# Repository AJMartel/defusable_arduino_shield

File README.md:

# Defusable Alarm Clock Shield for Arduino

Deze github bevat de software, datasheets en referentie materiaal incl. printplaat bestanden van het Defusable Alarm Clock Shield voor Arduino.

J.A. Korten - 2017

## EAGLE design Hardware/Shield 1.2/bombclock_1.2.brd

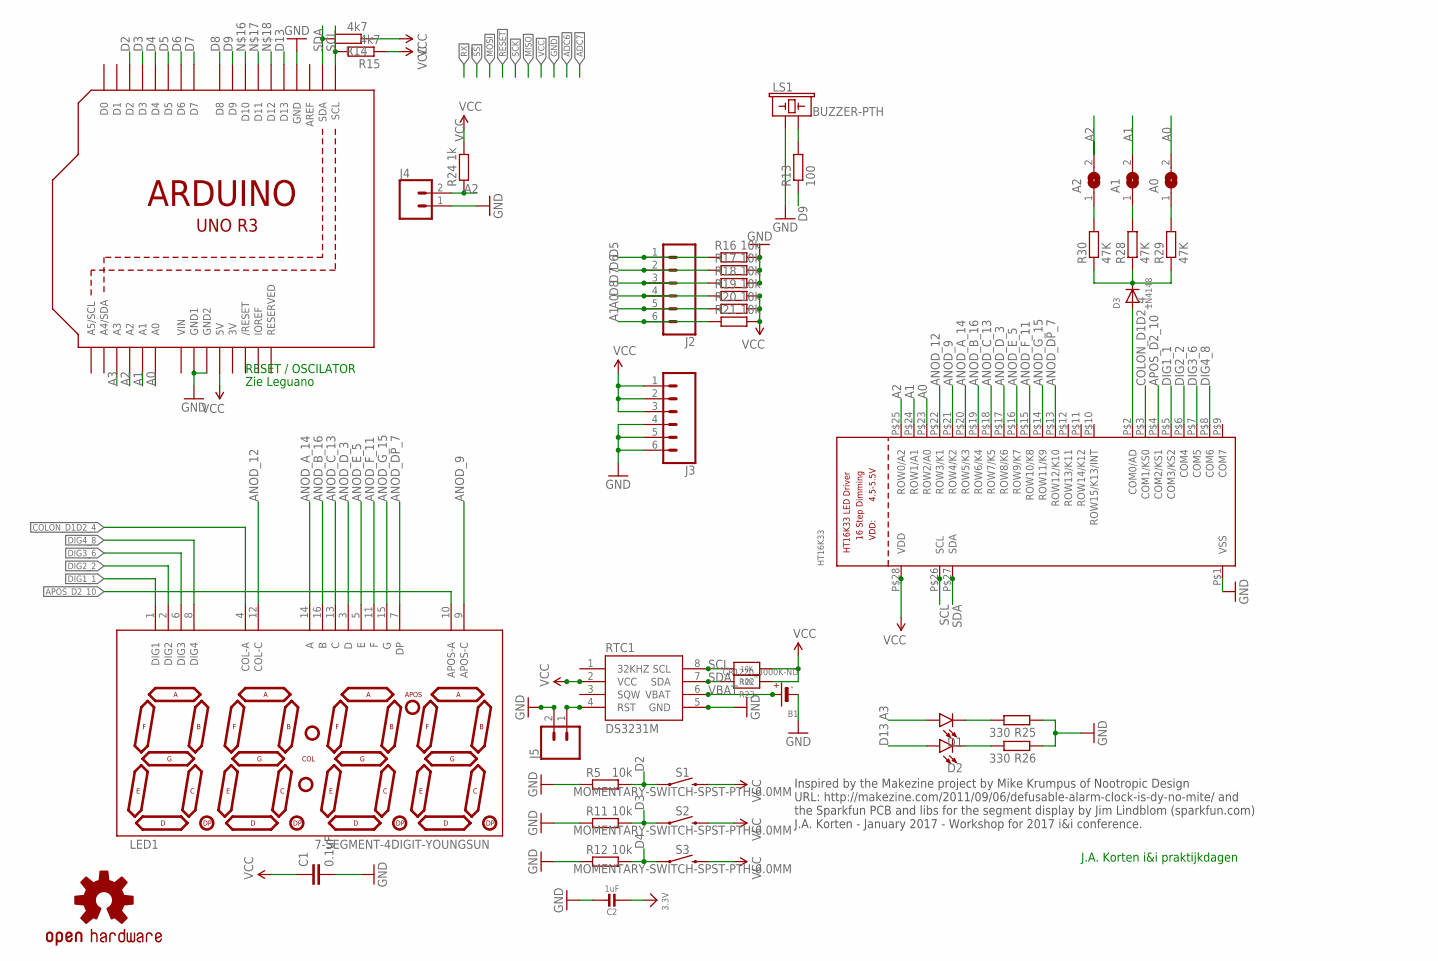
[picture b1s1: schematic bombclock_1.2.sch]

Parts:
A0, A1, A2: SOLDERJUMPERREFLOW_NOPASTE; SOLDERJUMPER_REFLOW_NOPASTE
B1: CR1220_3000K-ND; CR1220
C1: 0.1uF; 0402-CAP
C2: 1uF; 0805-NO
D1, D2: LED5MM; LED_5MM
D3: 1N4148; SOD-323F
HT16K33: HT16K33_SOP28; SOP28_300MIL
J2, J3: CONN_06SILK_FEMALE_PTH; 1X06
J4, J5: CONN_02; 1X02
LED1: 7-SEGMENT-4DIGIT-YOUNGSUN
LS1: BUZZER-PTH; BUZZER-12MM
R5, R11, R12, R16, R17, R18, R19, R20, R21: 10k; R0603
R13: 100; R0603
R14, R15: 4k7; R0603
R22, R23: 10K; 0805-NO
R24: 1k; R0603
R25, R26: 330; R0603
R28, R29, R30: 47K; R0603
RTC1: DS3231M; SO08
S1, S2, S3: MOMENTARY-SWITCH-SPST-PTH-6.0MM; TACTILE_SWITCH_PTH_6.0MM
U1: ARDUINOR3-DIMENSION; ARDUINOR3
U$4: OSHW-LOGOS; OSHW-LOGO-S

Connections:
3.3V: C2.2
3V: U1.3V
A0: A0.2, HT16K33.P$23 (ROW2/A0), J2.5, R20.1, U1.A0
A1: A1.2, HT16K33.P$24 (ROW1/A1), J2.6, R21.1, U1.A1
A2: A2.2, HT16K33.P$25 (ROW0/A2), J4.2, R24.1, U1.A2
A3: D1.A, U1.A3
ANOD_9: HT16K33.P$21 (ROW4/K2), LED1.9 (APOS-C)
ANOD_12: HT16K33.P$22 (ROW3/K1), LED1.12 (COL-C)
ANOD_A_14: HT16K33.P$20 (ROW5/K3), LED1.14 (A)
ANOD_B_16: HT16K33.P$19 (ROW6/K4), LED1.16 (B)
ANOD_C_13: HT16K33.P$18 (ROW7/K5), LED1.13 (C)
ANOD_DP_7: HT16K33.P$13 (ROW12/K10), LED1.7 (DP)
ANOD_D_3: HT16K33.P$17 (ROW8/K6), LED1.3 (D)
ANOD_E_5: HT16K33.P$16 (ROW9/K7), LED1.5 (E)
ANOD_F_11: HT16K33.P$15 (ROW10/K8), LED1.11 (F)
ANOD_G_15: HT16K33.P$14 (ROW11/K9), LED1.15 (G)
APOS_D2_10: HT16K33.P$4 (COM2/KS1), LED1.10 (APOS-A)
COLON_D1D2_4: HT16K33.P$3 (COM1/KS0), LED1.4 (COL-A)
D2: R5.2, S1.1, U1.D2
D3: R11.2, S2.1, U1.D3
D4: R12.2, S3.1, U1.D4
D5: J2.1, R16.1, U1.D5
D6: J2.2, R17.1, U1.D6
D7: J2.3, R18.1, U1.D7
D8: J2.4, R19.1, U1.D8
D9: R13.1, U1.D9
D13: D2.A, U1.D13
DIG1_1: HT16K33.P$5 (COM3/KS2), LED1.1 (DIG1)
DIG2_2: HT16K33.P$6 (COM4), LED1.2 (DIG2)
DIG3_6: HT16K33.P$7 (COM5), LED1.6 (DIG3)
DIG4_8: HT16K33.P$8 (COM6), LED1.8 (DIG4)
GND: B1.-, C1.2, C2.1, HT16K33.P$1 (VSS), J3.4, J3.5, J3.6, J4.1, J5.2, LS1.+ (1), R5.1, R11.1, R12.1, R16.2, R17.2, R18.2, R25.1, R26.1, RTC1.5 (GND), U1.GND, U1.GND1, U1.GND2
unnamed: A0.1, R29.2
unnamed: D3.A, HT16K33.P$2 (COM0/AD)
unnamed: D1.K (C), R25.2
unnamed: D2.K (C), R26.2
unnamed: A1.1, R28.2
unnamed: LS1.- (2), R13.2
unnamed: D3.C, R28.1, R29.1, R30.1
unnamed: A2.1, R30.2
PP: J5.1, RTC1.4 (RST)
SCL: HT16K33.P$26 (SCL), R15.2, R22.2, RTC1.8 (SCL), U1.SCL
SDA: HT16K33.P$27 (SDA), R14.2, R23.2, RTC1.7 (SDA), U1.SDA
VBAT: B1.+$1 (+), RTC1.6 (VBAT)
VCC: C1.1, HT16K33.P$28 (VDD), J3.1, J3.2, J3.3, R14.1, R15.1, R19.2, R20.2, R21.2, R22.1, R23.1, R24.2, RTC1.2 (VCC), S1.3 (2), S2.3 (2), S3.3 (2), U1.5V
VIN: U1.VIN

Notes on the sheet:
Inspired by the Makezine project by Mike Krumpus of Nootropic Design URL: http://makezine.com/2011/09/06/defusable-alarm-clock-is-dy-no-mite/ and the Sparkfun PCB and libs for the segment display by Jim Lindblom (sparkfun.com) J.A. Korten - January 2017 - Workshop for 2017 i&i conference.
RESET / OSCILATOR
Zie Leguano
J.A. Korten i&i praktijkdagen

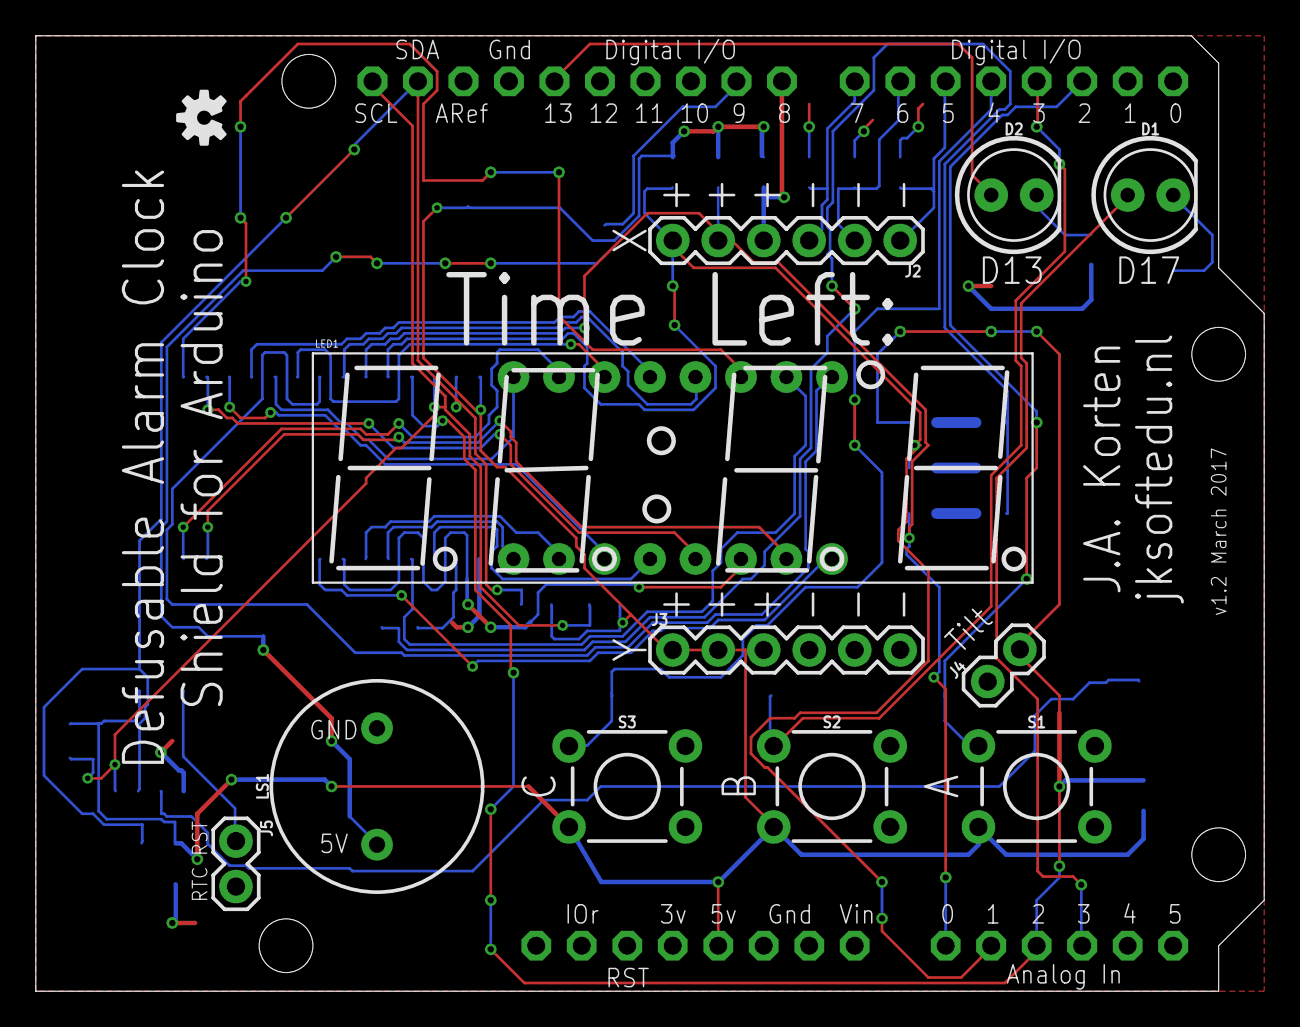
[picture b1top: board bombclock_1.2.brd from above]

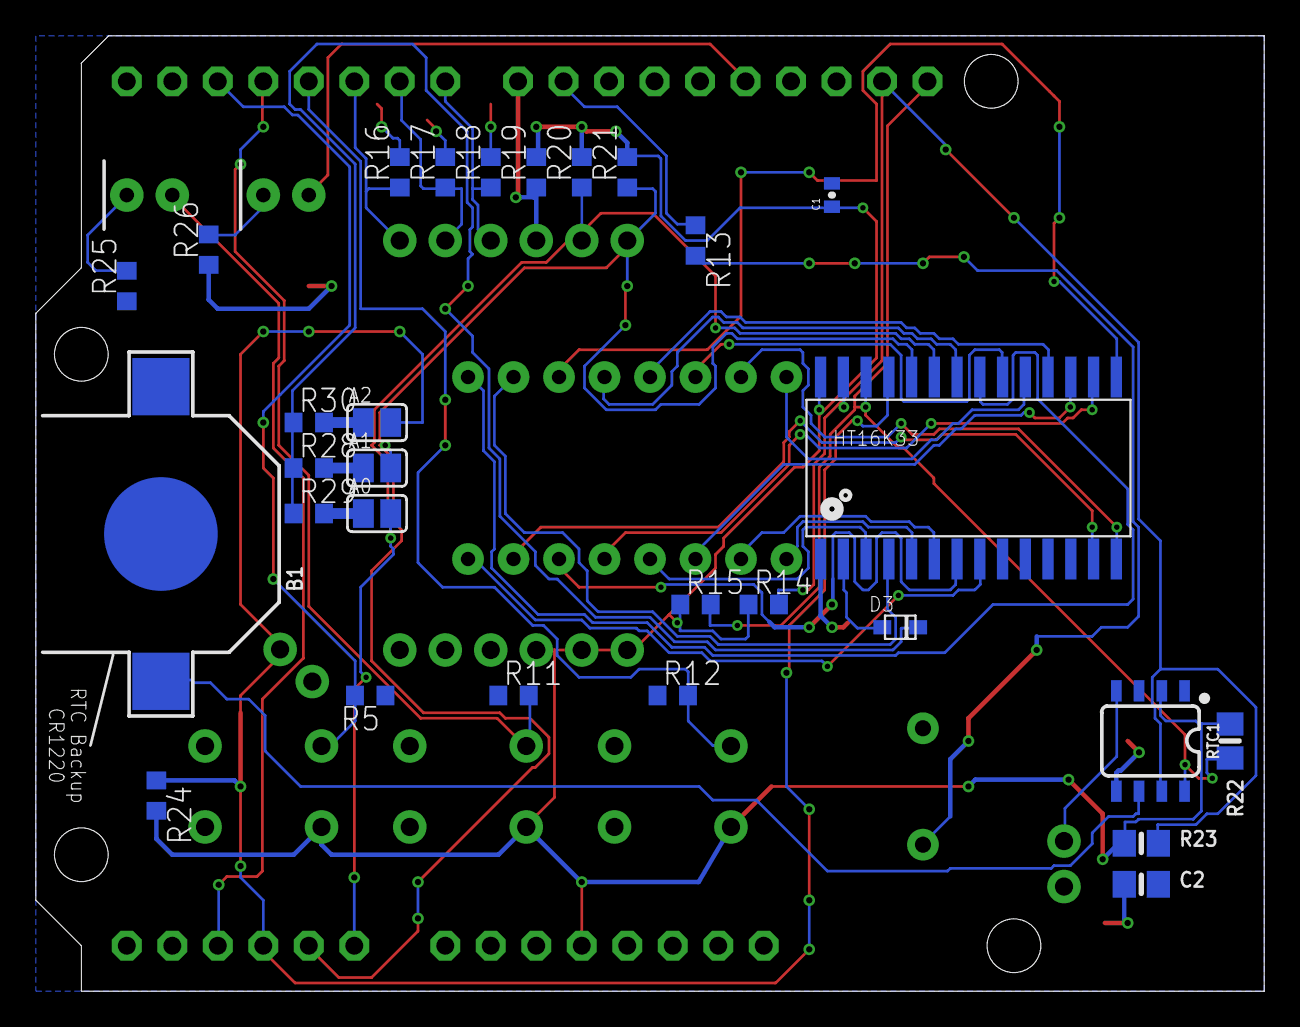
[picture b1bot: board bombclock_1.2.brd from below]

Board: 2 copper layers, 68.6 x 53.3 mm, 42 parts (29 on the bottom side), 43 nets.

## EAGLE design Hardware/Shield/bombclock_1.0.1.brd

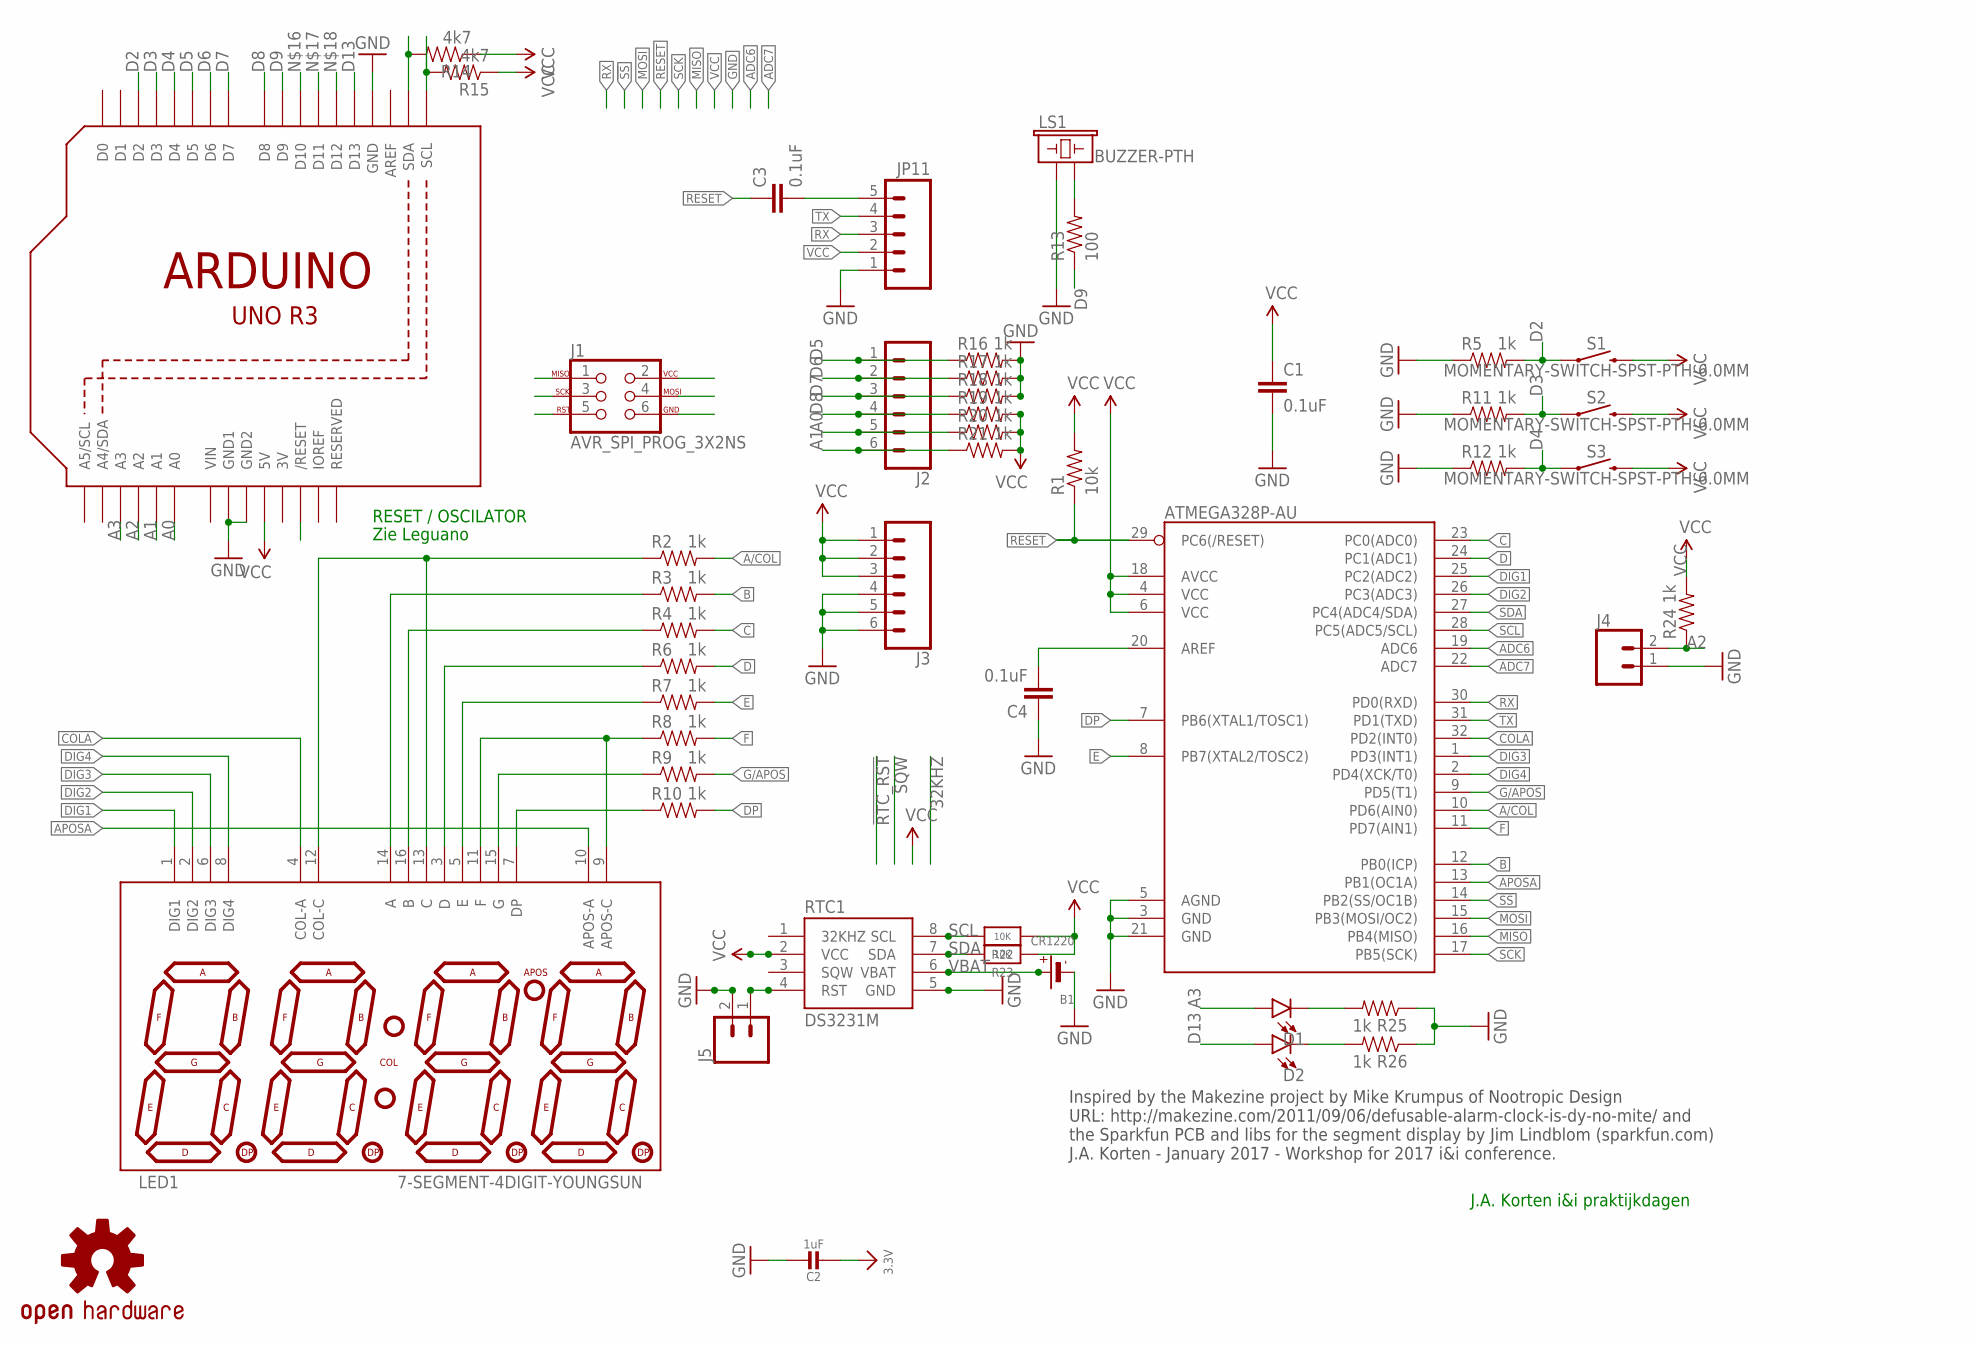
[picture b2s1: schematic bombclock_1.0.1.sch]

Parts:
ATMEGA328P-AU: ATMEGA328P-AU; TQFP32-08
B1: CR1220
C1, C3, C4: 0.1uF; 0402-CAP
C2: 1uF; 0805-NO
D1, D2: LED5MM; LED_5MM
J1: AVR_SPI_PROG_3X2NS; 2X3-NS
J2, J3: CONN_06SILK_FEMALE_PTH; 1X06
J4, J5: CONN_02; 1X02
JP11: M05PTH-NS; 1X05_NO_SILK
LED1: 7-SEGMENT-4DIGIT-YOUNGSUN
LS1: BUZZER-PTH; BUZZER-12MM
R1: 10k; 0402-RES
R2, R3, R4, R5, R6, R7, R8, R9, R10, R11, R12, R16, R17, R18, R19, R20, R21, R24, R25, R26: 1k; 0402-RES
R13: 100; 0402-RES
R14, R15: 4k7; 0402-RES
R22, R23: 10K; 0805-NO
RTC1: DS3231M; SO08
S1, S2, S3: MOMENTARY-SWITCH-SPST-PTH-6.0MM; TACTILE_SWITCH_PTH_6.0MM
U1: ARDUINOR3-DIMENSION; ARDUINOR3
U$4: OSHW-LOGOS; OSHW-LOGO-S

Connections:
3.3V: C2.2
3V: U1.3V
!SS: ATMEGA328P-AU.14 (PB2(SS/OC1B))
A0: J2.5, R20.1, U1.A0
A1: J2.6, R21.1, U1.A1
A2: J4.2, R24.1, U1.A2
A3: D1.A, U1.A3
A/COL: ATMEGA328P-AU.10 (PD6(AIN0)), R2.2
ADC6: ATMEGA328P-AU.19 (ADC6)
ADC7: ATMEGA328P-AU.22 (ADC7)
APOSA: ATMEGA328P-AU.13 (PB1(OC1A)), LED1.10 (APOS-A)
B: ATMEGA328P-AU.12 (PB0(ICP)), R3.2
C: ATMEGA328P-AU.23 (PC0(ADC0)), R4.2
COLA: ATMEGA328P-AU.32 (PD2(INT0)), LED1.4 (COL-A)
D: ATMEGA328P-AU.24 (PC1(ADC1)), R6.2
D2: R5.2, S1.1, U1.D2
D3: R11.2, S2.1, U1.D3
D4: R12.2, S3.1, U1.D4
D5: J2.1, R16.1, U1.D5
D6: J2.2, R17.1, U1.D6
D7: J2.3, R18.1, U1.D7
D8: J2.4, R19.1, U1.D8
D9: R13.1, U1.D9
D13: D2.A, U1.D13
DIG1: ATMEGA328P-AU.25 (PC2(ADC2)), LED1.1 (DIG1)
DIG2: ATMEGA328P-AU.26 (PC3(ADC3)), LED1.2 (DIG2)
DIG3: ATMEGA328P-AU.1 (PD3(INT1)), LED1.6 (DIG3)
DIG4: ATMEGA328P-AU.2 (PD4(XCK/T0)), LED1.8 (DIG4)
DP: ATMEGA328P-AU.7 (PB6(XTAL1/TOSC1)), R10.2
E: ATMEGA328P-AU.8 (PB7(XTAL2/TOSC2)), R7.2
F: ATMEGA328P-AU.11 (PD7(AIN1)), R8.2
G/APOS: ATMEGA328P-AU.9 (PD5(T1)), R9.2
GND: ATMEGA328P-AU.3 (GND), ATMEGA328P-AU.5 (AGND), ATMEGA328P-AU.21 (GND), B1.-, C1.2, C2.1, C4.1, J1.6, J3.4, J3.5, J3.6, J4.1, J5.2, JP11.1, LS1.+ (1), R5.1, R11.1, R12.1, R16.2, R17.2, R18.2, R25.1, R26.1, RTC1.5 (GND), U1.GND, U1.GND1, U1.GND2
MISO: ATMEGA328P-AU.16 (PB4(MISO)), J1.1
MOSI: ATMEGA328P-AU.15 (PB3(MOSI/OC2)), J1.4
unnamed: ATMEGA328P-AU.20 (AREF), C4.2
unnamed: LED1.7 (DP), R10.1
unnamed: LED1.15 (G), R9.1
unnamed: LED1.9 (APOS-C), LED1.11 (F), R8.1
unnamed: LED1.5 (E), R7.1
unnamed: LED1.3 (D), R6.1
unnamed: LED1.16 (B), R4.1
unnamed: LED1.14 (A), R3.1
unnamed: LED1.12 (COL-C), LED1.13 (C), R2.1
unnamed: D1.K (C), R25.2
unnamed: C3.2, JP11.5
unnamed: D2.K (C), R26.2
unnamed: LS1.- (2), R13.2
PP: J5.1, RTC1.4 (RST)
RESET: ATMEGA328P-AU.29 (PC6(/RESET)), C3.1, J1.5, R1.1
RST_UNO: U1.RESET (/RESET)
RX: ATMEGA328P-AU.30 (PD0(RXD)), JP11.3
SCK: ATMEGA328P-AU.17 (PB5(SCK)), J1.3
SCL: ATMEGA328P-AU.28 (PC5(ADC5/SCL)), R15.2, R22.2, RTC1.8 (SCL), U1.SCL
SDA: ATMEGA328P-AU.27 (PC4(ADC4/SDA)), R14.2, R23.2, RTC1.7 (SDA), U1.SDA
TX: ATMEGA328P-AU.31 (PD1(TXD)), JP11.4
VBAT: B1.+$1 (+), RTC1.6 (VBAT)
VCC: ATMEGA328P-AU.4 (VCC), ATMEGA328P-AU.6 (VCC), ATMEGA328P-AU.18 (AVCC), C1.1, J1.2, J3.1, J3.2, J3.3, JP11.2, R1.2, R14.1, R15.1, R19.2, R20.2, R21.2, R22.1, R23.1, R24.2, RTC1.2 (VCC), S1.3 (2), S2.3 (2), S3.3 (2), U1.5V
VIN: U1.VIN

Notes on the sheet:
Inspired by the Makezine project by Mike Krumpus of Nootropic Design URL: http://makezine.com/2011/09/06/defusable-alarm-clock-is-dy-no-mite/ and the Sparkfun PCB and libs for the segment display by Jim Lindblom (sparkfun.com) J.A. Korten - January 2017 - Workshop for 2017 i&i conference.
RESET / OSCILATOR
Zie Leguano
J.A. Korten i&i praktijkdagen

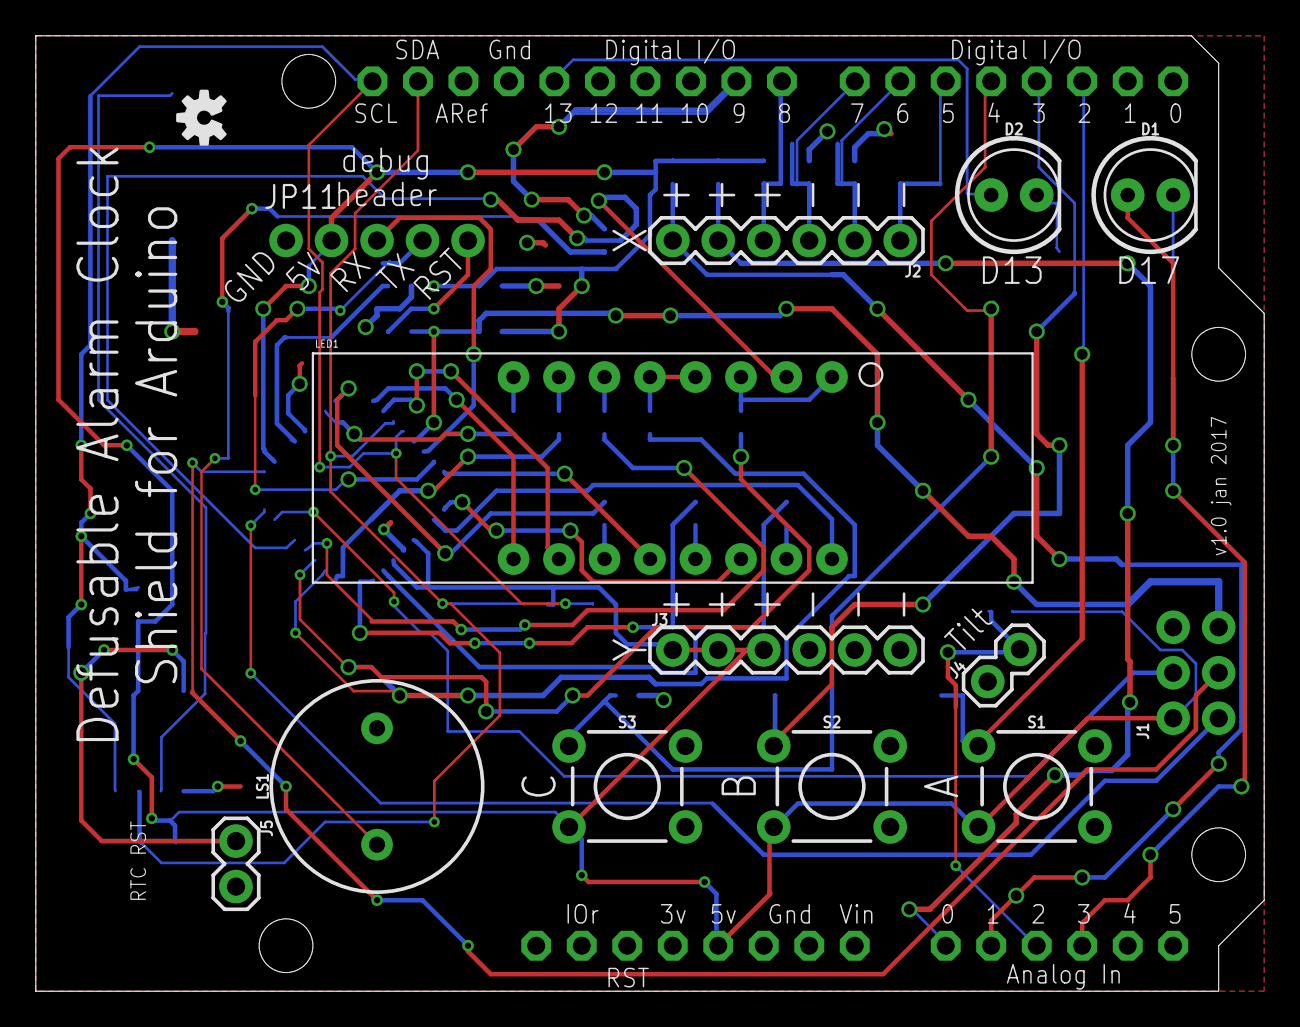
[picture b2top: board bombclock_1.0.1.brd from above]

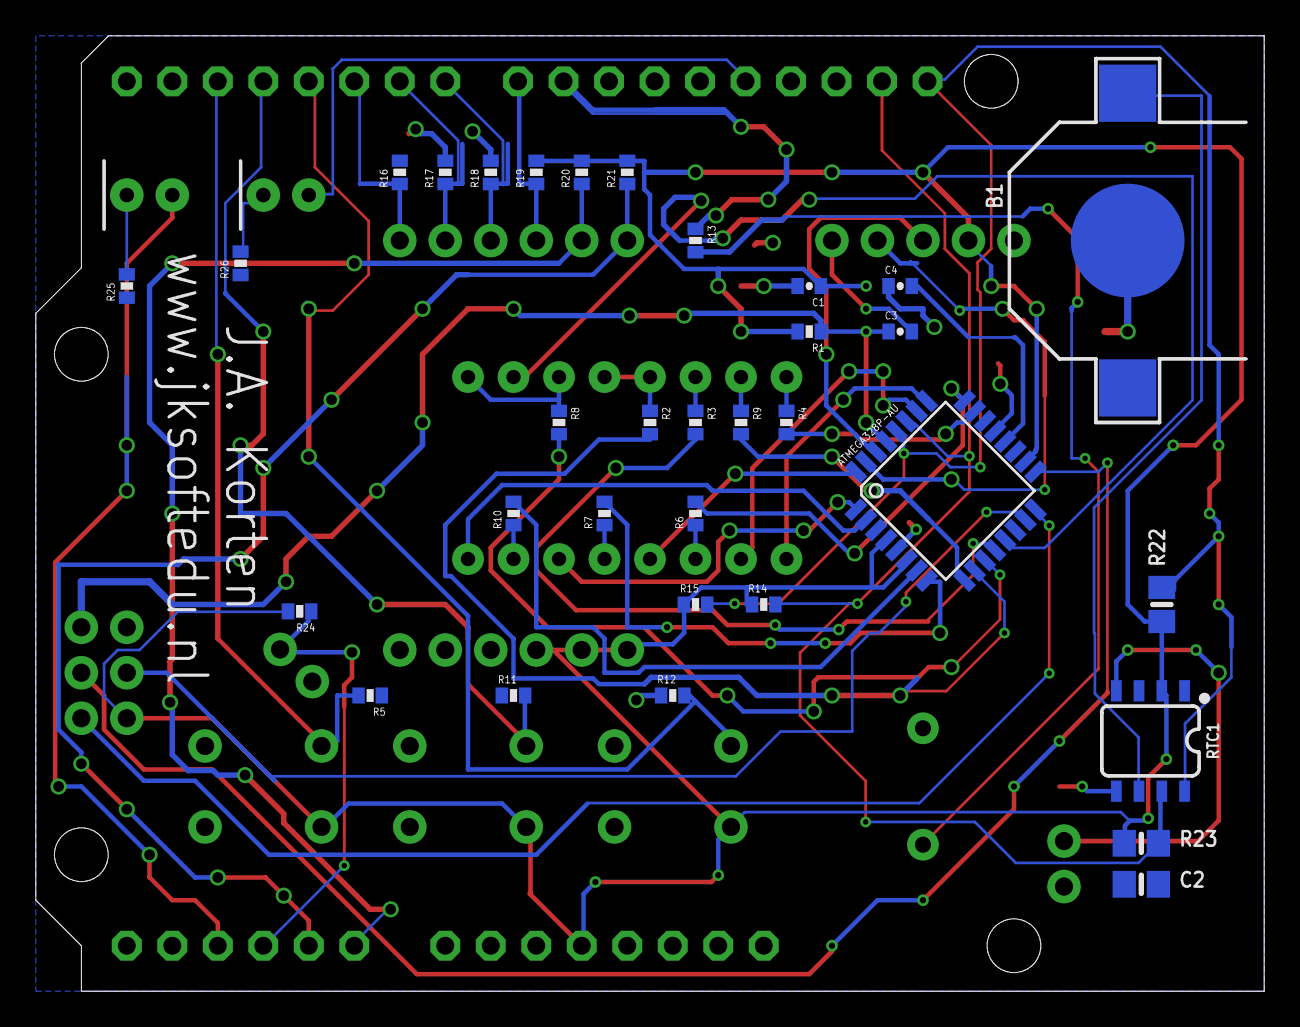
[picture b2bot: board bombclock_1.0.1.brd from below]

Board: 2 copper layers, 68.6 x 53.3 mm, 48 parts (33 on the bottom side), 52 nets.

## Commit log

2017-01-31 Example files
    Example files
2017-01-31 Aanpassingen en code
    Aanpassingen en code
2017-01-31 Updates
    Updates
2017-04-17 Updated library
    Updated library
2017-04-17 Added example
    Added example for use without library
2017-04-17 MegaBomb example
    MegaBomb example
2017-04-17 Updated example MegaBomb
    Updated example MegaBomb
2017-04-17 Restructured examples
    Restructured examples
2017-04-17 Booklet update
2017-04-18 Added i2c scanner
    Added i2c scanner
2017-04-19 Booklet update
    Update
2017-04-19 Updates Booklet
    Updates Booklet
2017-04-19 Added HT16K33 datasheet
    Added HT16K33 datasheet
2017-04-19 Added: presentations
    Presentations added
2017-04-19 Final update keynote
    Final update keynote
2017-04-19 Update van de presentatie
    Update van de presentatie, foutjes opgelost.

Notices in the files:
parts and their libraries:
SparkFun-Electromechanical: Licensing: Creative Commons ShareAlike 4.0 International - https://creativecommons.org/licenses/by-sa/4.0
SparkFun-Connectors: Licensing: CC v3.0 Share-Alike You are welcome to use this library for commercial purposes.
